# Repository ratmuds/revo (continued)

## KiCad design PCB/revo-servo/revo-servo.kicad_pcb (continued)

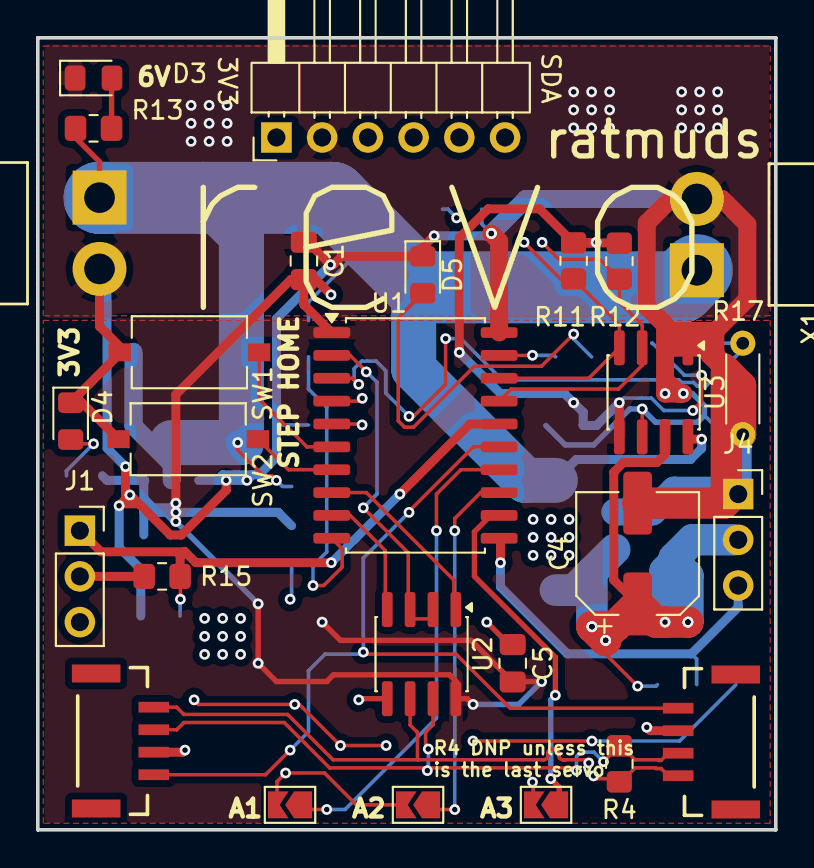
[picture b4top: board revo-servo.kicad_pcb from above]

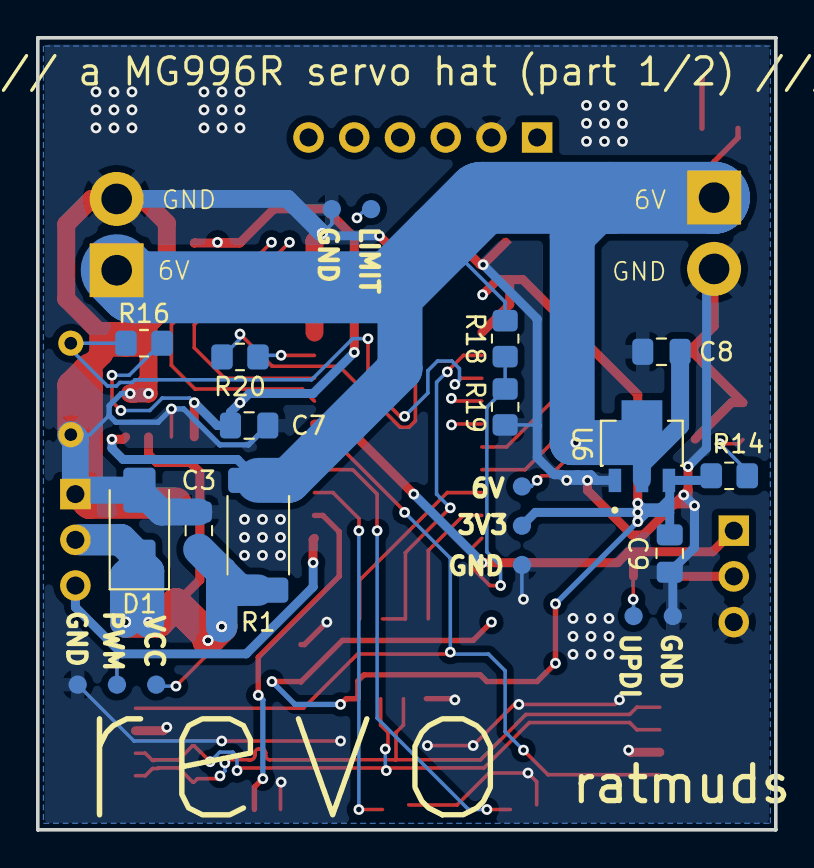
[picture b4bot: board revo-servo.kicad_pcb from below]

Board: 4 copper layers, 41.0 x 44.0 mm, 49 parts (22 on the bottom side), 28 nets.

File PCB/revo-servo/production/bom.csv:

Designator,Footprint,Quantity,Value,LCSC Part #
"C1, C3, C5, C7",0805,4,0.1uF,
C4,CP_Elec_6.3x5.4,1,100uF,
"C8, C9",0805,2,10uF,
D1,D_SMA,1,SS34,
"D3, D4, D5",0805,3,LED,
J1,PinSocket_1x03_P2.54mm_Vertical,1,Programming,
J2,JST_1x04_P1.25mm_Locking_Horizontal_SMD,1,Data In,
J3,JST_1x04_P1.25mm_Locking_Horizontal_SMD,1,Data Out,
J4,PinSocket_1x03_P2.54mm_Vertical,1,Motor,
J6,PinHeader_1x06_P2.54mm_Horizontal,1,Sensor Board Connector,
"JP1, JP2, JP3",SolderJumper-2_P1.3mm_Open_TrianglePad1.0x1.5mm,3,Jumper_2_Open,
R1,2512,1,0.1R 2W,
"R11, R12, R15",0805,3,4.7k,
R13,0805,1,330R,
"R14, R20",0805,2,220R,
"R16, R19",0805,2,10k,
R17,R_Axial_DIN0204_L3.6mm_D1.6mm_P5.08mm_Horizontal,1,NTC 10k,
R18,0805,1,20k,
R4,0805,1,120R,
SW1,SW_Tactile_SPST_NO_Straight_CK_PTS636Sx25SMTRLFS,1,Home,
SW2,SW_Tactile_SPST_NO_Straight_CK_PTS636Sx25SMTRLFS,1,Step,
"TP1, TP10, TP2, TP3, TP4, TP5, TP6, TP7, TP8, TP9",TestPoint-1.0mm,10,1.0mm,
U1,SOIC-20W_7.5x12.8mm_P1.27mm,1,ATtiny3216-S,
U2,SOIC-8_3.9x4.9mm_P1.27mm,1,THVD1420D,
U3,SOIC-8_3.9x4.9mm_P1.27mm,1,INA219AxD,
U6,IC_HT7333,1,HT7333,
X1,B2PS-VH,1,Power,
X2,B2PS-VH,1,Power Out,

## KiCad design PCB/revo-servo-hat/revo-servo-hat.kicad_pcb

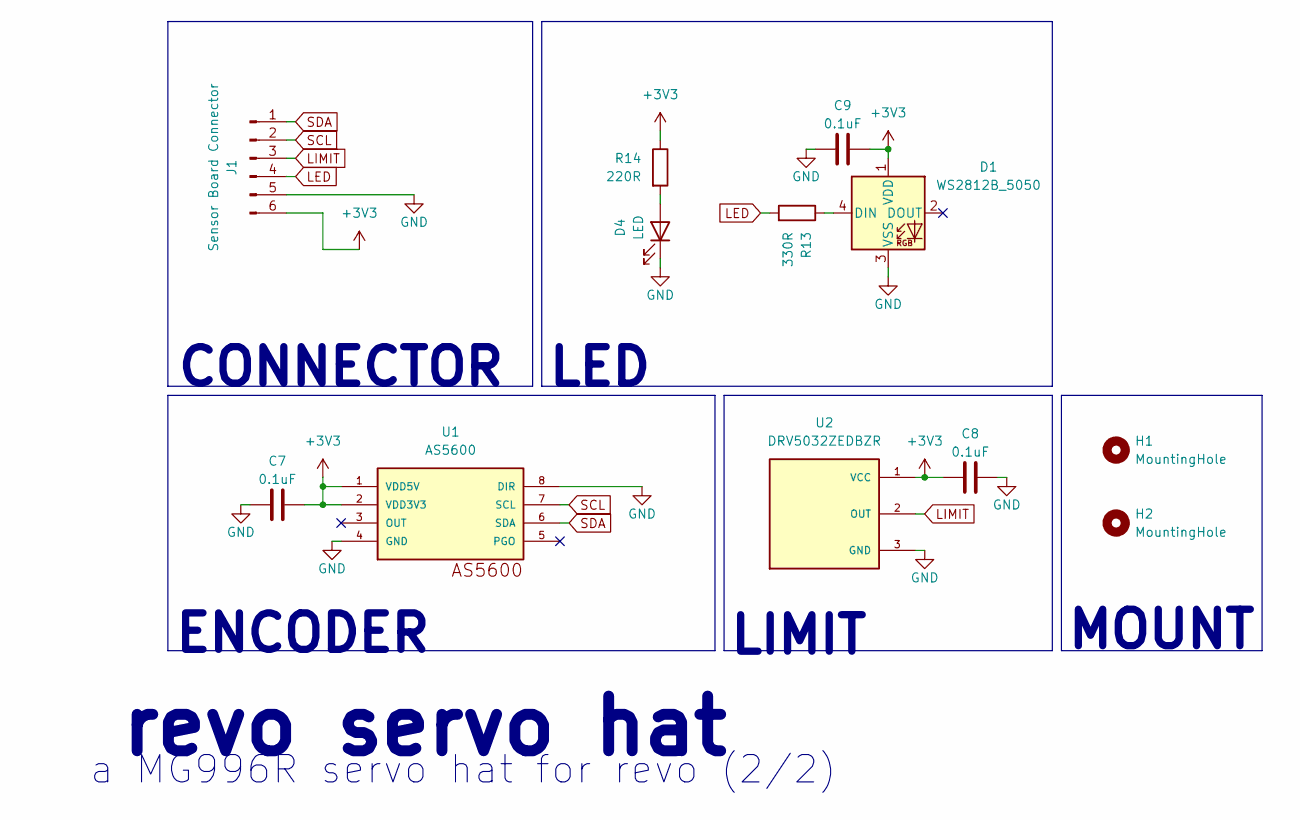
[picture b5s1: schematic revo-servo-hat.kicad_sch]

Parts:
C7, C8, C9: 0.1uF; C_0805_2012Metric_Pad1.18x1.45mm_HandSolder
D1: WS2812B_5050; LED_WS2812B_PLCC4_5.0x5.0mm_P3.2mm
D4: LED; D_0805_2012Metric_Pad1.15x1.40mm_HandSolder
H1, H2: MountingHole; MountingHole_3.2mm_M3
J1: Sensor Board Connector; PinHeader_1x06_P2.54mm_Horizontal
R13: 330R; R_0805_2012Metric_Pad1.20x1.40mm_HandSolder
R14: 220R; R_0805_2012Metric_Pad1.20x1.40mm_HandSolder
U1: AS5600; SOIC8
U2: DRV5032ZEDBZR; SOT95P237X112-3N; PARTREV F

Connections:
+3V3: C7.2, C8.1, C9.2, D1.1 (VDD), J1.6, R14.1, U1.1 (VDD5V), U1.2 (VDD3V3), U2.1 (VCC)
GND: C7.1, C8.2, C9.1, D1.3 (VSS), D4.1 (K), J1.5, U1.4 (GND), U1.8 (DIR), U2.3 (GND)
LED: J1.4, R13.2
LIMIT: J1.3, U2.2 (OUT)
unnamed: D1.4 (DIN), R13.1
unnamed: D4.2 (A), R14.2
SCL: J1.2, U1.7 (SCL)
SDA: J1.1, U1.6 (SDA)

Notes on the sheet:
a MG996R servo hat for revo (2/2)
LIMIT
ENCODER
MOUNT
CONNECTOR
revo servo hat
LED

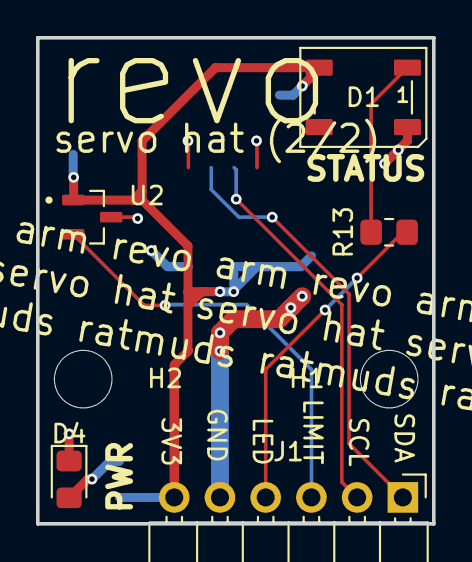
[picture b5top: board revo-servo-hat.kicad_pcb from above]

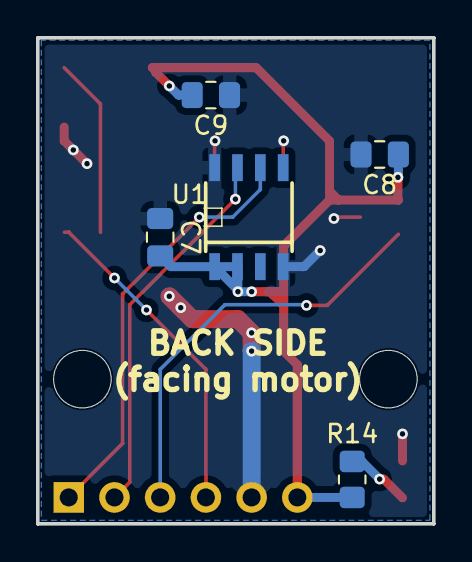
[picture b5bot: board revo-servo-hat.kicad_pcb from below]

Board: 2 copper layers, 22.0 x 27.0 mm, 12 parts (5 on the bottom side), 8 nets.

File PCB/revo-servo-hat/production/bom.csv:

Designator,Footprint,Quantity,Value,LCSC Part #
"C7, C8, C9",0805,3,0.1uF,
D1,LED_WS2812B_PLCC4_5.0x5.0mm_P3.2mm,1,WS2812B_5050,
D4,0805,1,LED,
J1,PinHeader_1x06_P2.54mm_Horizontal,1,Sensor Board Connector,
R13,0805,1,330R,
R14,0805,1,220R,
U1,SOIC8,1,AS5600,
U2,SOT95P237X112-3N,1,DRV5032ZEDBZR,

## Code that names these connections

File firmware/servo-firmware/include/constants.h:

#ifndef CONSTANTS_H
#define CONSTANTS_H

#include <Arduino.h>

#define DATA_LED PIN_PA3
#define RS485_DE PIN_PA4
#define NEOPIXEL_PIN PIN_PA6
#define MAGNET_PIN PIN_PA7 // DRV5032 Hall Effect Sensor on PA7
#define NTC_PIN PIN_PA5    // NTC Thermistor on PA5
#define VOLTAGE_PIN                                                            \
  PIN_PB1 // Voltage divider on PB1 (nominal 6V, 20k top, 10k bot)

#define BUTTON_STEP PIN_PB4 // STEP push button (active LOW)
#define BUTTON_HOME PIN_PB5 // HOME push button (active LOW)

#define ADDR_A1 PIN_PC2 // Address Pin Bit 0 (LSB)
#define ADDR_A2 PIN_PC1 // Address Pin Bit 1
#define ADDR_A3 PIN_PC0 // Address Pin Bit 2 (MSB)

#define FIXED_CPR 54000LL // Fixed counts per revolution (360 deg)
#define TICKS_OFFSET -200

// Continuous servo: 90=stop. < 90 is forward, > 90 is backward/reverse.
#define HOMING_SPEED 70         // Forward reference speed (90 - 20)
#define HOMING_REV_SPEED 110    // Backward seek speed towards magnet (90 + 20)
#define HOMING_JOG_FWD_SPEED 70 // Slow forward jog to clear magnet (90 - 10)
#define HOMING_JOG_REV_SPEED                                                   \
  105 // Slow backward jog to latch magnet edge (90 + 10)
#define HOMING_MAX_COUNTS                                                      \
  54000LL // Max reverse rotation before safety abort (~360 deg)
#define POS_DEADBAND                                                           \
  30 // raw counts: within this of target we consider "arrived"
#define POS_SLOWDOWN                                                           \
  600 // raw counts error at which duty-cycle pulsing / deceleration begins
#define POS_MIN_SPEED                                                          \
  7 // min speed offset to overcome servo deadband (97 fwd / 83 rev)
#define POS_MAX_SPEED 45 // 50% max speed/torque offset (45..135 PWM)
#define POS_CYCLE_MS                                                           \
  60 // PWM flickering period in ms (e.g. 60ms = 3 servo refresh frames)
#define POS_MIN_ON_MS 20 // minimum pulse ON time in ms for micro-stepping taps
#define PACKET_TIMEOUT_MS                                                      \
  1500 // No valid packet within this window -> "no connection"
#define PACKET_MAGIC                                                           \
  0xA5 // Sync byte: detects wrong/junk firmware or garbage on the bus

// --- Per-PCB Servo Hardware Profiles (Direction flip & PWM speed multiplier)
// ---
struct ServoHardwareProfile {
  bool flipDirection;    // Invert direction around 90 (true if servo spins
                         // opposite)
  float speedMultiplier; // Multiplier on (PWM - 90) offset (e.g. 0.5 for fast
                         // servos)
};

#define NUM_SERVO_PROFILES 8

// Configuration indexed by PCB Hardware ID (0 to 7)
const ServoHardwareProfile SERVO_PROFILES[NUM_SERVO_PROFILES] = {
    {false, 1.0f}, // ID 0: Standard
    {true, 0.5f},  // ID 1: Flipped direction & 0.5x speed
    {false, 1.0f}, // ID 2: Standard
    {false, 1.0f}, // ID 3: Standard
    {false, 1.0f}, // ID 4: Standard
    {false, 1.0f}, // ID 5: Standard
    {false, 1.0f}, // ID 6: Standard
    {false, 1.0f}, // ID 7: Standard
};

#endif // CONSTANTS_H

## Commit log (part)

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2026-06-01 initial commit - about to order PCBs
